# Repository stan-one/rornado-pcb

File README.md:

# tornado-pcb
PCB schematic and BOM

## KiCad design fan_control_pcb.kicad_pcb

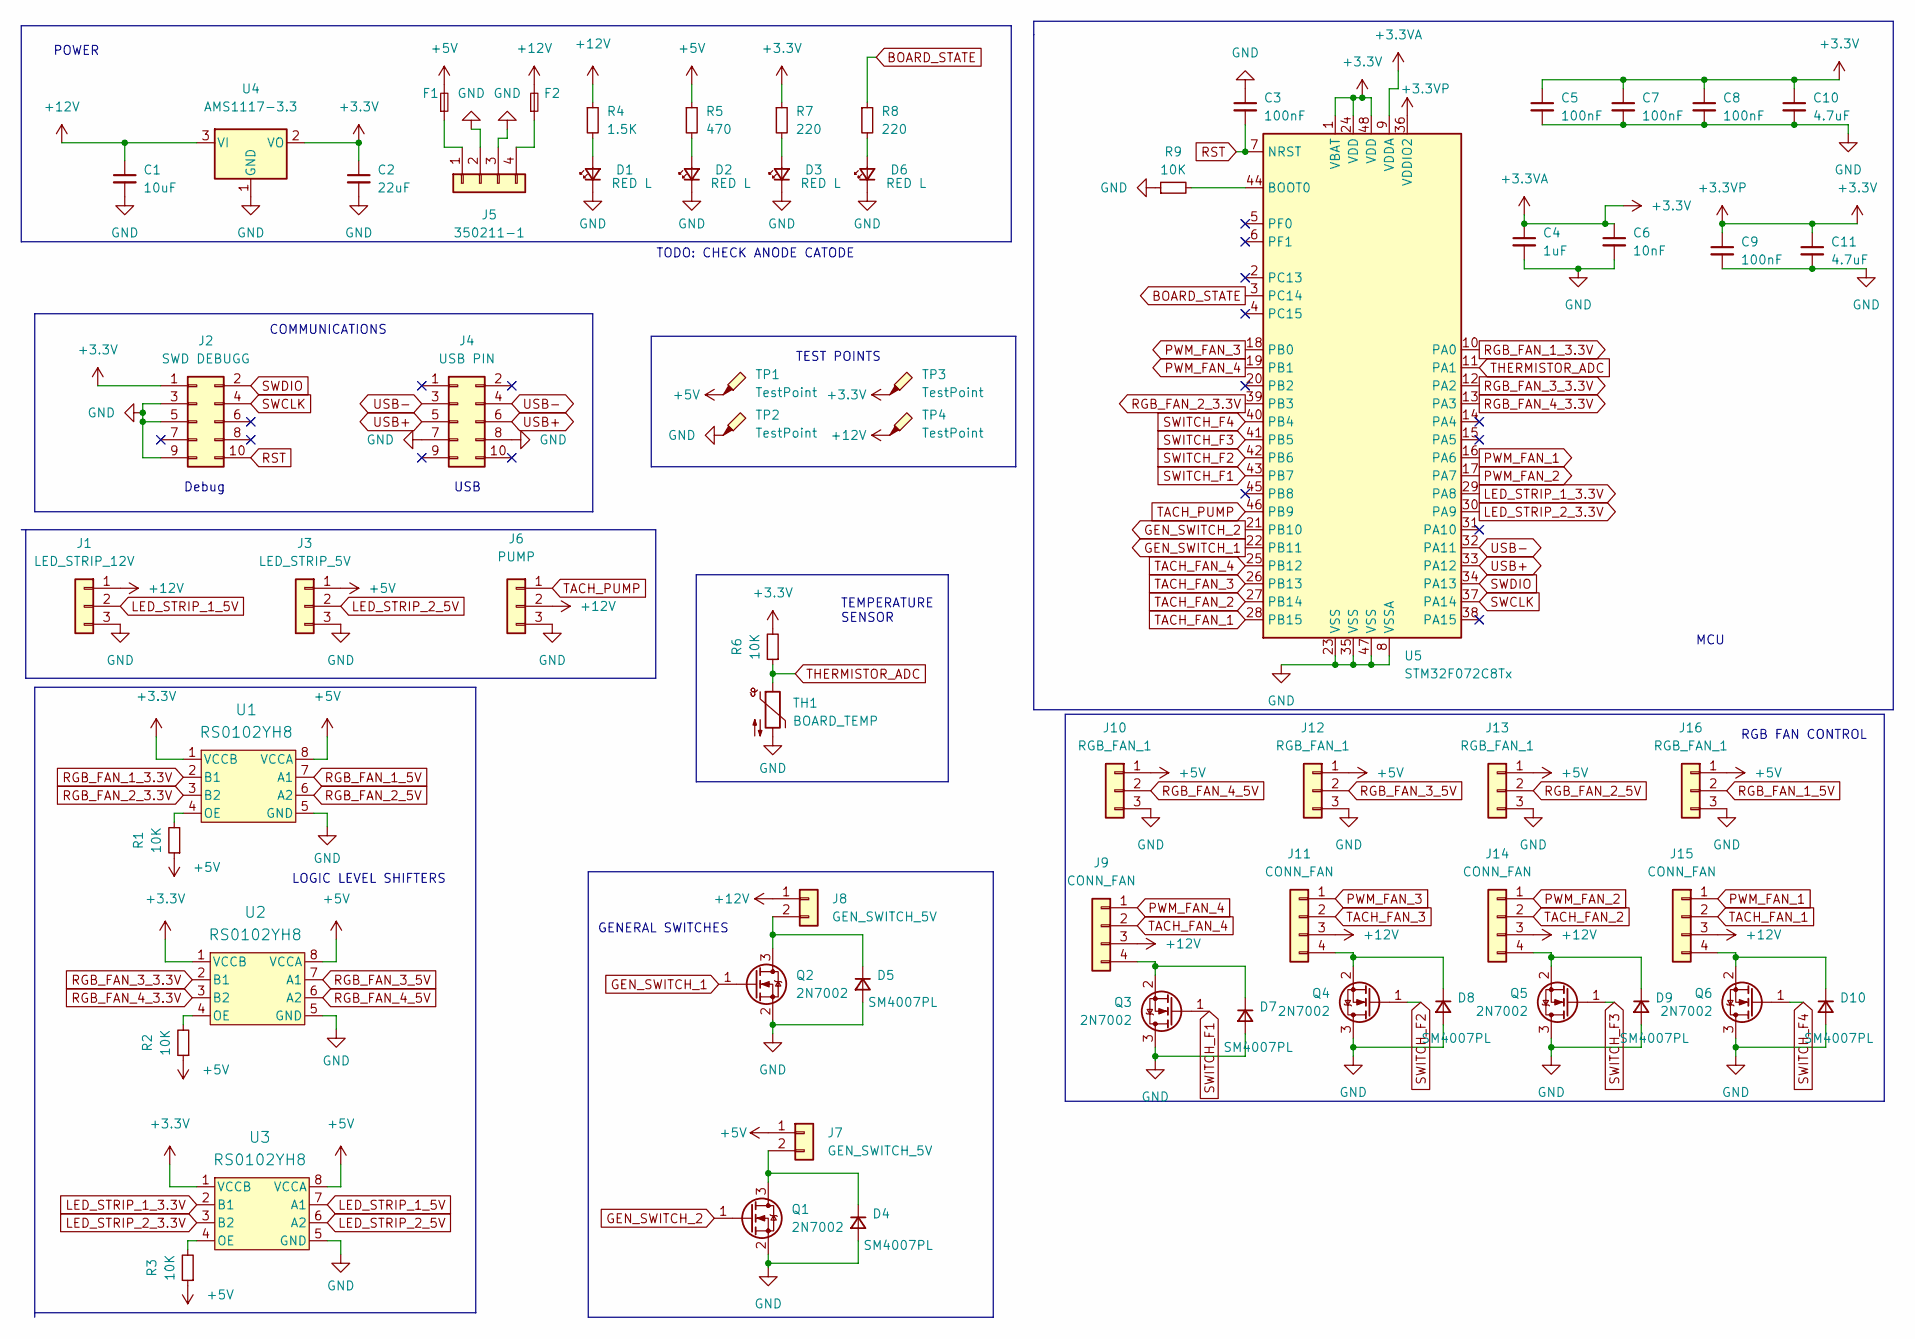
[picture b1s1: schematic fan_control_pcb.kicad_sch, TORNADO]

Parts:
C1: 10uF; C_0603_1608Metric
C2: 22uF; C_0603_1608Metric
C3, C5, C7, C8, C9: 100nF; C_0603_1608Metric
C4: 1uF; C_0603_1608Metric
C6: 10nF; C_0603_1608Metric
C10, C11: 4.7uF; C_0603_1608Metric
D1, D2, D3, D6: RED L; LED_0603_1608Metric
D4, D5, D7, D8, D9, D10: SM4007PL; D_SOD-123F
F1, F2: Fuse_Small; Fuse_0805_2012Metric
J1: LED_STRIP_12V; PinHeader_1x03_P2.54mm_Horizontal
J2: SWD DEBUGG; PinHeader_2x05_P1.27mm_Vertical
J3: LED_STRIP_5V; PinHeader_1x03_P2.54mm_Horizontal
J4: USB PIN; PinHeader_2x05_P2.54mm_Horizontal
J5: 350211-1; TerminalBlock_bornier-4_P5.08mm
J6: PUMP; PinHeader_1x03_P2.54mm_Horizontal
J7, J8: GEN_SWITCH_5V; PinHeader_1x02_P2.54mm_Horizontal
J9, J11, J14, J15: CONN_FAN; PinHeader_1x04_P2.54mm_Horizontal
J10, J12, J13, J16: RGB_FAN_1; PinHeader_1x03_P2.54mm_Horizontal
Q1, Q2, Q3, Q4, Q5, Q6: 2N7002; SOT-23
R1, R2, R3, R6, R9: 10K; R_0603_1608Metric
R4: 1.5K; R_0603_1608Metric
R5: 470; R_0603_1608Metric
R7, R8: 220; R_0603_1608Metric
TH1: BOARD_TEMP; R_0603_1608Metric
TP1, TP2, TP3, TP4: TestPoint; TestPoint_Pad_D1.5mm
U1, U2, U3: RS0102YH8; SOT-23-8
U4: AMS1117-3.3; SOT-223-3_TabPin2
U5: STM32F072C8Tx; LQFP-48_7x7mm_P0.5mm

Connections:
+3.3V: C2.1, C4.1, C5.1, C6.1, C7.1, C8.1, C9.1, C10.1, C11.1, J2.1, R6.2, R7.1, TP3.1, U1.1 (VCCB), U2.1 (VCCB), U3.1 (VCCB), U4.2 (VO), U5.1 (VBAT), U5.9 (VDDA), U5.24 (VDD), U5.36 (VDDIO2), U5.48 (VDD)
+5V: F1.2, J3.1, J7.1, J10.1, J12.1, J13.1, J16.1, R1.1, R2.1, R3.1, R5.1, TP1.1, U1.8 (VCCA), U2.8 (VCCA), U3.8 (VCCA)
+12V: C1.1, F2.2, J1.1, J6.2, J8.1, J9.3, J11.3, J14.3, J15.3, R4.1, TP4.1, U4.3 (VI)
BOARD_STATE: R8.1, U5.3 (PC14)
GEN_SWITCH_1: Q2.1 (G), U5.22 (PB11)
GEN_SWITCH_2: Q1.1 (G), U5.21 (PB10)
GND: C1.2, C2.2, C3.1, C4.2, C5.2, C6.2, C7.2, C8.2, C9.2, C10.2, C11.2, D1.2 (K), D2.2 (K), D3.2 (K), D4.2 (A), D5.2 (A), D6.2 (K), D7.2 (A), D8.2 (A), D9.2 (A), D10.2 (A), J1.3, J2.3, J2.5, J2.9, J3.3, J4.7, J4.8, J5.2, J5.3, J6.3, J10.3, J12.3, J13.3, J16.3, Q1.2 (S), Q2.2 (S), Q3.3 (D), Q4.3 (D), Q5.3 (D), Q6.3 (D), R9.1, TH1.2, TP2.1, U1.5 (GND), U2.5 (GND), U3.5 (GND), U4.1 (GND), U5.8 (VSSA), U5.23 (VSS), U5.35 (VSS), U5.47 (VSS)
LED_STRIP_1_3.3V: U3.2 (B1), U5.29 (PA8)
LED_STRIP_1_5V: J1.2, U3.7 (A1)
LED_STRIP_2_3.3V: U3.3 (B2), U5.30 (PA9)
LED_STRIP_2_5V: J3.2, U3.6 (A2)
unnamed: D1.1 (A), R4.2
unnamed: D2.1 (A), R5.2
unnamed: D3.1 (A), R7.2
unnamed: D4.1 (K), J7.2, Q1.3 (D)
unnamed: D5.1 (K), J8.2, Q2.3 (D)
unnamed: D6.1 (A), R8.2
unnamed: D7.1 (K), J9.4, Q3.2 (S)
unnamed: D8.1 (K), J11.4, Q4.2 (S)
unnamed: D9.1 (K), J14.4, Q5.2 (S)
unnamed: D10.1 (K), J15.4, Q6.2 (S)
unnamed: F1.1, J5.1
unnamed: F2.1, J5.4
unnamed: R1.2, U1.4 (OE)
unnamed: R2.2, U2.4 (OE)
unnamed: R3.2, U3.4 (OE)
unnamed: R9.2, U5.44 (BOOT0)
PWM_FAN_1: J15.1, U5.16 (PA6)
PWM_FAN_2: J14.1, U5.17 (PA7)
PWM_FAN_3: J11.1, U5.18 (PB0)
PWM_FAN_4: J9.1, U5.19 (PB1)
RGB_FAN_1_3.3V: U1.2 (B1), U5.10 (PA0)
RGB_FAN_1_5V: J16.2, U1.7 (A1)
RGB_FAN_2_3.3V: U1.3 (B2), U5.39 (PB3)
RGB_FAN_2_5V: J13.2, U1.6 (A2)
RGB_FAN_3_3.3V: U2.2 (B1), U5.12 (PA2)
RGB_FAN_3_5V: J12.2, U2.7 (A1)
RGB_FAN_4_3.3V: U2.3 (B2), U5.13 (PA3)
RGB_FAN_4_5V: J10.2, U2.6 (A2)
RST: C3.2, J2.10, U5.7 (NRST)
SWCLK: J2.4, U5.37 (PA14)
SWDIO: J2.2, U5.34 (PA13)
SWITCH_F1: Q3.1 (G), U5.43 (PB7)
SWITCH_F2: Q4.1 (G), U5.42 (PB6)
SWITCH_F3: Q5.1 (G), U5.41 (PB5)
SWITCH_F4: Q6.1 (G), U5.40 (PB4)
TACH_FAN_1: J15.2, U5.28 (PB15)
TACH_FAN_2: J14.2, U5.27 (PB14)
TACH_FAN_3: J11.2, U5.26 (PB13)
TACH_FAN_4: J9.2, U5.25 (PB12)
TACH_PUMP: J6.1, U5.46 (PB9)
THERMISTOR_ADC: R6.1, TH1.1, U5.11 (PA1)
USB+: J4.5, J4.6, U5.33 (PA12)
USB-: J4.3, J4.4, U5.32 (PA11)

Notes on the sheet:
TEMPERATURE SENSOR
LOGIC LEVEL SHIFTERS
RGB FAN CONTROL
GENERAL SWITCHES
TEST POINTS
Debug
TODO: CHECK ANODE CATODE
COMMUNICATIONS
POWER
MCU
USB

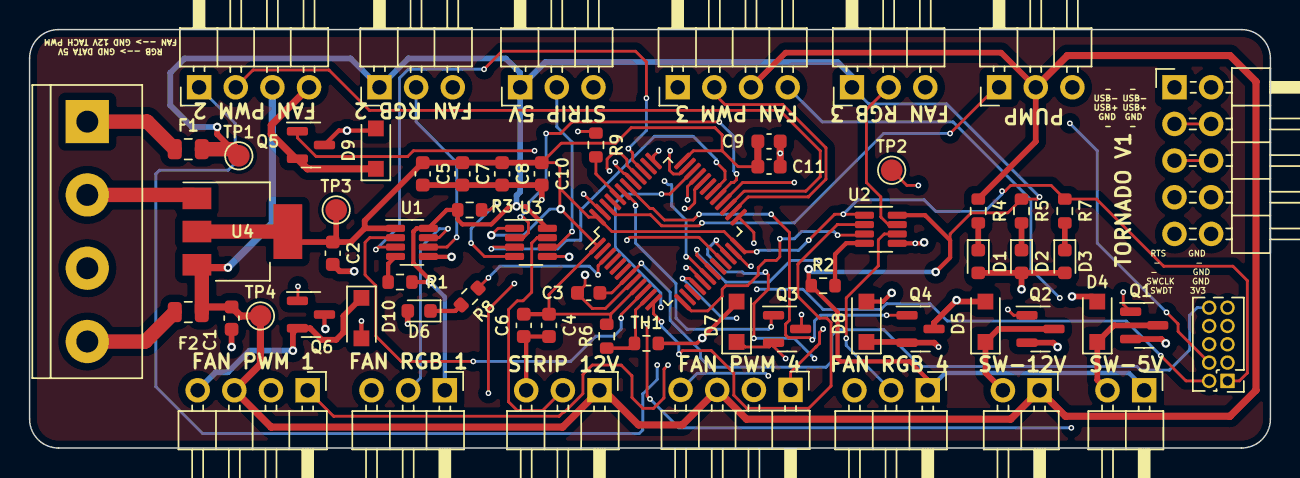
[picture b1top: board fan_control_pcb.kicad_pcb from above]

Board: 4 copper layers, 86.0 x 29.0 mm, 64 parts (0 on the bottom side), 54 nets.

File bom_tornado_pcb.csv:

Collated Components:,,,,,,
,,,,,,
Item,Qty,Reference(s),Value,LibPart,Footprint,PN
1,1,C1,10uF,Device:C_Small,Capacitor_SMD:C_0603_1608Metric,CL10A106MA8NRNC
2,1,C2,22uF,Device:C_Small,Capacitor_SMD:C_0603_1608Metric,CL10A226MQ8NRNC
3,5,"C3, C5, C7, C8, C9",100nF,Device:C_Small,Capacitor_SMD:C_0603_1608Metric,CC0603KRX7R9BB104
4,1,C4,1uF,Device:C_Small,Capacitor_SMD:C_0603_1608Metric,CL10A105KB8NNNC
5,1,C6,10nF,Device:C_Small,Capacitor_SMD:C_0603_1608Metric,0603B103K500NT
6,2,"C10, C11",4.7uF,Device:C_Small,Capacitor_SMD:C_0603_1608Metric,CL10A475KO8NNNC
7,4,"D1, D2, D3, D6",RED L,Device:LED_Small,LED_SMD:LED_0603_1608Metric,KT-0603R
8,6,"D4, D5, D7, D8, D9, D10",SM4007PL,Device:D_Small,Diode_SMD:D_SOD-123F,SM4007PL
9,2,"F1, F2",Fuse_Small,Device:Fuse_Small,Fuse:Fuse_0805_2012Metric,TODO
10,1,J1,LED_STRIP_12V,Connector_Generic:Conn_01x03,Connector_PinHeader_2.54mm:PinHeader_1x03_P2.54mm_Horizontal,PZ254-1-03-W-8.5
11,1,J2,SWD DEBUGG,Connector_Generic:Conn_02x05_Odd_Even,Connector_PinHeader_1.27mm:PinHeader_2x05_P1.27mm_Vertical,20021111-00010T4LF
12,1,J3,LED_STRIP_5V,Connector_Generic:Conn_01x03,Connector_PinHeader_2.54mm:PinHeader_1x03_P2.54mm_Horizontal,PZ254-1-03-W-8.5
13,1,J4,USB PIN ,Connector_Generic:Conn_02x05_Odd_Even,Connector_PinHeader_2.54mm:PinHeader_2x05_P2.54mm_Horizontal,A2541WR-2x5P
14,1,J5,350211-1,Connector_Generic:Conn_01x04,TerminalBlock:TerminalBlock_bornier-4_P5.08mm,350211-1
15,1,J6,PUMP,Connector_Generic:Conn_01x03,Connector_PinHeader_2.54mm:PinHeader_1x03_P2.54mm_Horizontal,PZ254-1-03-W-8.5
16,2,"J7, J8",GEN_SWITCH_5V,Connector_Generic:Conn_01x02,Connector_PinHeader_2.54mm:PinHeader_1x02_P2.54mm_Horizontal,B-2100S02P-A110
17,4,"J9, J11, J14, J15",CONN_FAN,Connector_Generic:Conn_01x04,Connector_PinHeader_2.54mm:PinHeader_1x04_P2.54mm_Horizontal,    PZ254-1-04-W-8.5
18,4,"J10, J12, J13, J16",RGB_FAN_1,Connector_Generic:Conn_01x03,Connector_PinHeader_2.54mm:PinHeader_1x03_P2.54mm_Horizontal,PZ254-1-03-W-8.5
19,6,"Q1, Q2, Q3, Q4, Q5, Q6",2N7002,Transistor_FET:2N7002,Package_TO_SOT_SMD:SOT-23,2N7002
20,5,"R1, R2, R3, R6, R9",10K,Device:R_Small,Resistor_SMD:R_0603_1608Metric,0603WAF510KT5E
21,1,R4,1.5K,Device:R_Small,Resistor_SMD:R_0603_1608Metric,0603WAF1501T5E
22,1,R5,470,Device:R_Small,Resistor_SMD:R_0603_1608Metric,0603WAF4700T5E
23,2,"R7, R8",220,Device:R_Small,Resistor_SMD:R_0603_1608Metric,0603WAF2200T5E
24,1,TH1,BOARD_TEMP,Device:Thermistor_NTC,Resistor_SMD:R_0603_1608Metric,NCP18XH103F03RB
25,4,"TP1, TP2, TP3, TP4",TestPoint,Connector:TestPoint_Probe,TestPoint:TestPoint_Pad_D1.5mm,NONE
26,3,"U1, U2, U3",RS0102YH8,RS0102YH8:RS0102YH8,Package_TO_SOT_SMD:SOT-23-8,RS0102YH8
27,1,U4,AMS1117-3.3,Regulator_Linear:AZ1117-3.3,Package_TO_SOT_SMD:SOT-223-3_TabPin2,AMS1117-3.3
28,1,U5,STM32F072C8Tx,MCU_ST_STM32F0:STM32F072C8Tx,Package_QFP:LQFP-48_7x7mm_P0.5mm,STM32F072C8T6
